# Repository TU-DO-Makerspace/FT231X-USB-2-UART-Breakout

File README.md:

# FT231X USB 2 UART Breakout

This repository features a USB 2 UART converter/breakout board built on the FTDI FT231X IC. Although numerous affordable USB to UART converters are readily available on the market, this particular one was designed around a spare FT231X IC soldered to a SMD break-out adapter we had in our lab. Figured we'd make use of it then! The PCB was designed with a single-board layout in consideration, as we etched the PCB oursevles.

We don't really expect anyone to use this design, but we're making it available for archival purposes in case it breaks down some day or someone is simply curious about the design. However, if you do happen to find it useful, that's pretty awesome too!

## Schematic

The schematic pretty much provides the bare minimum to use the FT231X IC as a USB to UART converter. Some notable features include:

- A switch to switch between 3.3V and 5V logic levels
- LEDs to indicate power and data transmission
- Exposed supply, RX, TX, RTS, CTS, DTR, DSR, DCD, and RI pins
- Exposed CBUS pins for custom functionality

The data transmission LEDs have been implemented via the RX/TX lines. While it is possible to use the CBUS pins for this purpose, we decided to use the RX/TX lines to keep all CBUS pins exposed.

The schematic KiCAD file can be found in the `kicad` directory.

## PCB

The PCB was designed to be self-etched, and as such, it is a single-layer board. The front copper layer is only used to visualize jumpers. We used the "toner transfer method" to etch the PCB, which allows us to print a silk screen on to the non-conductive layer.

The PCB was designed in a way where the right side of the board breaks out the FT231X pins with angled 2.54mm male headers. The side of the board is then meant to "stick out" of the enclosure to allow for easy access to the pins. We also make heavy use of JST connectors so that the board can easily be removed from the enclosure and repaired or modified if necessary. The front silk-screen indicates the pinout of the FT231X IC, as well as the pinout of the JST connectors. This was done to make it easier to use the board without having to refer to the schematic.

The PCB KiCAD file can be found in the `kicad` directory.

## Enclosure

The enclosure was designed for 3D printing, intended to house most of the PCB, while leaving the right side of the board exposed for easy access to the break-out pins. This design choice also allows the silk-screen to be utilized for identifying the functionality of the break-out pins.

The 3mf files for the enclosure can be found in the `enclosure` directory.

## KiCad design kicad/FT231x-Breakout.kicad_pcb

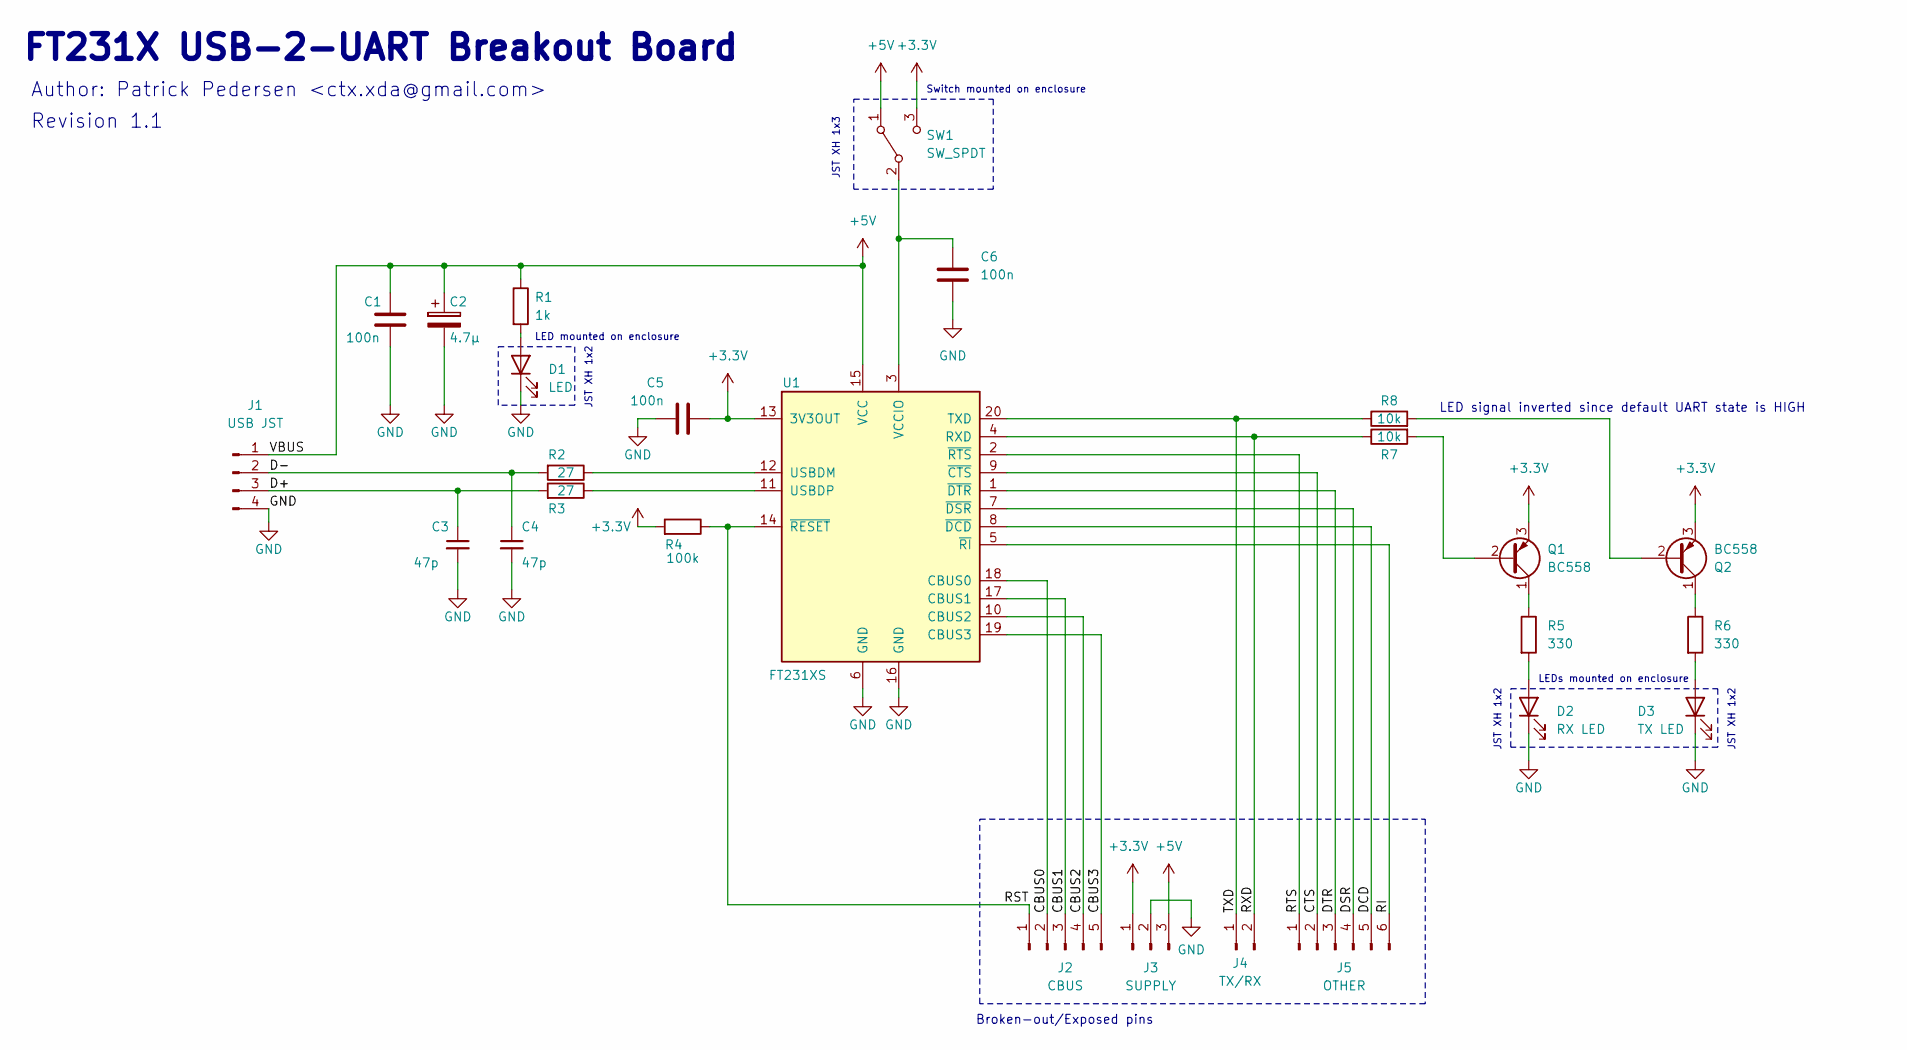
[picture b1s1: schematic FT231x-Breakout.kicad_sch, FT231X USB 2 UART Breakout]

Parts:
C1, C5, C6: 100n; C_Disc_D3.0mm_W2.0mm_P2.50mm
C2: 4.7µ; CP_Radial_D5.0mm_P2.00mm
C3, C4: 47p; C_Disc_D3.0mm_W2.0mm_P2.50mm
D1: LED; JST_XH_B2B-XH-A_1x02_P2.50mm_Vertical
D2: RX LED; JST_XH_B2B-XH-A_1x02_P2.50mm_Vertical
D3: TX LED; JST_XH_B2B-XH-A_1x02_P2.50mm_Vertical
J1: USB JST; JST_XH_B4B-XH-A_1x04_P2.50mm_Vertical
J2: CBUS; PinHeader_1x05_P2.54mm_Horizontal
J3: SUPPLY; PinHeader_1x03_P2.54mm_Horizontal
J4: TX/RX; PinHeader_1x02_P2.54mm_Horizontal
J5: OTHER; PinHeader_1x06_P2.54mm_Horizontal
Q1, Q2: BC558; TO-92_HandSolder
R1: 1k; R_Axial_DIN0207_L6.3mm_D2.5mm_P7.62mm_Horizontal
R2, R3: 27; R_Axial_DIN0207_L6.3mm_D2.5mm_P7.62mm_Horizontal
R4: 100k; R_Axial_DIN0207_L6.3mm_D2.5mm_P7.62mm_Horizontal
R5, R6: 330; R_Axial_DIN0207_L6.3mm_D2.5mm_P7.62mm_Horizontal
R7, R8: 10k; R_Axial_DIN0207_L6.3mm_D2.5mm_P7.62mm_Horizontal
SW1: SW_SPDT; JST_XH_B3B-XH-A_1x03_P2.50mm_Vertical
U1: FT231XS; FTDI231X_Breakout

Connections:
+3.3V: C5.2, J3.1, Q1.3 (E), Q2.3 (E), R4.2, SW1.3 (C), U1.13 (3V3OUT)
+5V: C1.1, C2.1, J1.1, J3.3, R1.1, SW1.1 (A), U1.15 (VCC)
/CBUS0: J2.2, U1.18 (CBUS0)
/CBUS1: J2.3, U1.17 (CBUS1)
/CBUS2: J2.4, U1.10 (CBUS2)
/CBUS3: J2.5, U1.19 (CBUS3)
/CTS: J5.2, U1.9 (~CTS)
/D+: C3.1, J1.3, R3.2
/D-: C4.1, J1.2, R2.2
/DCD: J5.5, U1.8 (~DCD)
/DSR: J5.4, U1.7 (~DSR)
/DTR: J5.3, U1.1 (~DTR)
/RI: J5.6, U1.5 (~RI)
/RST: J2.1, R4.1, U1.14 (~RESET)
/RTS: J5.1, U1.2 (~RTS)
/RXD: J4.2, R7.1, U1.4 (RXD)
/TXD: J4.1, R8.1, U1.20 (TXD)
GND: C1.2, C2.2, C3.2, C4.2, C5.1, C6.2, D1.1 (K), D2.1 (K), D3.1 (K), J1.4, J3.2, U1.6 (GND), U1.16 (GND)
unnamed: D1.2 (A), R1.2
unnamed: D2.2 (A), R5.2
unnamed: D3.2 (A), R6.2
unnamed: Q1.2 (B), R7.2
unnamed: Q1.1 (C), R5.1
unnamed: Q2.2 (B), R8.2
unnamed: Q2.1 (C), R6.1
unnamed: C6.1, SW1.2 (B), U1.3 (VCCIO)
unnamed: R2.1, U1.12 (USBDM)
unnamed: R3.1, U1.11 (USBDP)

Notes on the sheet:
FT231X USB-2-UART Breakout Board
JST XH 1x2
Broken-out/Exposed pins
LED mounted on enclosure
LED signal inverted since default UART state is HIGH
JST XH 1x3
Switch mounted on enclosure
LEDs mounted on enclosure
Revision 1.1
Author: Patrick Pedersen <ctx.xda@gmail.com>

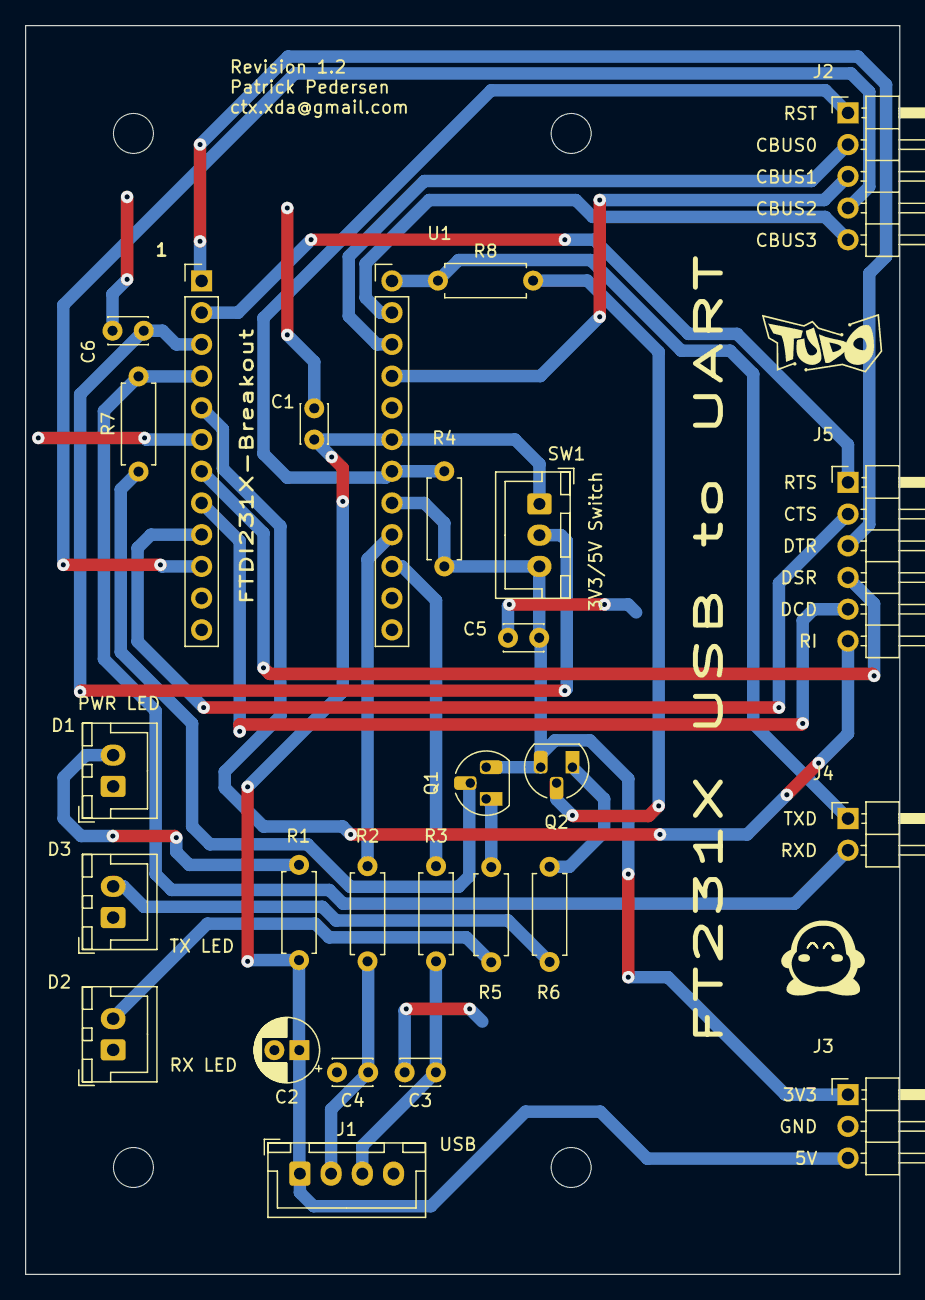
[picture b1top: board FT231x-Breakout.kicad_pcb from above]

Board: 2 copper layers, 70.0 x 100.0 mm, 26 parts (0 on the bottom side), 28 nets.

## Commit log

2024-02-06 Initial commit of Rev 1.0 (with fixed Labels)
2024-02-06 Rev1.1
2024-02-27 Rev 1.2 + Added README
2024-02-27 Added enclosure files
2024-02-27 Kicad: Moved breakout footprint to kicad dir

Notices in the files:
FT231x-Breakout.kicad_sch:
License: CERN-OHL-P
